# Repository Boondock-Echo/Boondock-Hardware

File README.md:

# Boondock-Hardware
Hardware Design Files, BOM, Assembly Instructions, etc.

# Hardware

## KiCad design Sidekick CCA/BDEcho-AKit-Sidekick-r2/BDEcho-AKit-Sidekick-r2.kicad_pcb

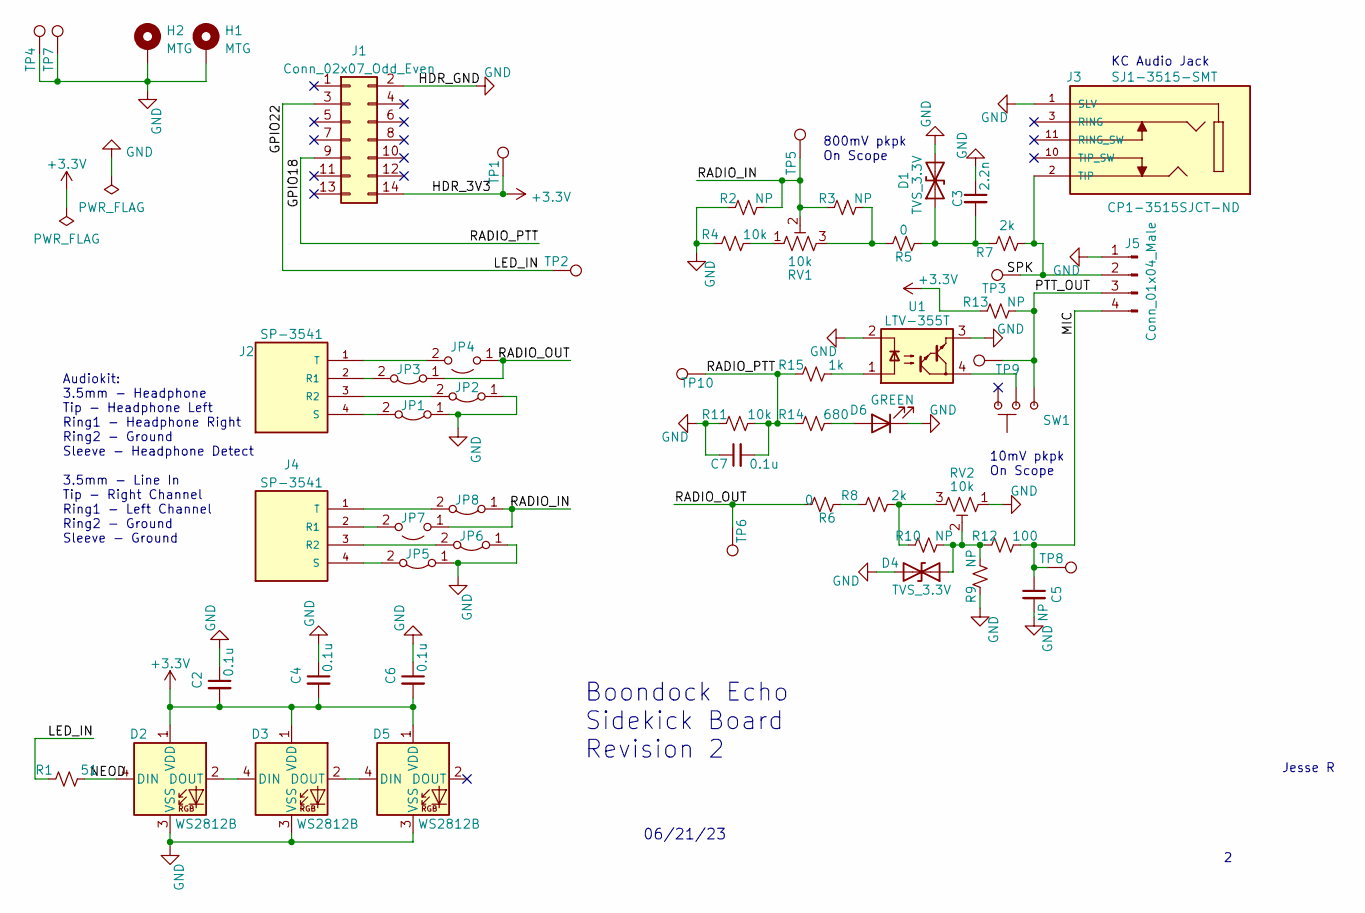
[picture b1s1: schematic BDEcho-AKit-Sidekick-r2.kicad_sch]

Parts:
C2, C4, C6, C7: 0.1u; C_0805_2012Metric; LCSC C1711
C3: 2.2n; C_0805_2012Metric; MFG # CL21C222JBFNNNE; JLCPCB C28260
C5: NP; C_0805_2012Metric; MFG # NA; JLCPCB NA
D1, D4: TVS_3.3V; D_SOD-123; MFG # BZT52C3V3; JLCPCB C2891770
D2, D3, D5: WS2812B; LED_WS2812B_PLCC4; MFG # WS2812B-B/W; JLCPCB C2761795
D6: GREEN; LED_0805_2012Metric; LCSC C73548
H1, H2: MTG; MountingHole_2.7mm_M2.5_ISO7380_Pad; LCSC NA
J1: Conn_02x07_Odd_Even; PinHeader_2x07_P2.54mm_Vertical; LCSC C400039
J2, J4: SP-3541; SP-3541_Makerfabs_2; PART_REV 1.0; LCSC MFABS
J3: SJ1-3515-SMT; CUI_SJ1-3515-SMT; PARTREV 1.05; JLCPCB NA
J5: Conn_01x04_Male; PinHeader_1x04_P2.54mm_Vertical; LCSC NA
JP1, JP2, JP3, JP5, JP6, JP8: JMP; SolderJumper-2_P1.3mm_Bridged2Bar_RoundedPad1.0x1.5mm; LCSC NA
JP4, JP7: JMP; SolderJumper-2_P1.3mm_Open_RoundedPad1.0x1.5mm; LCSC NA
R1: 51; R_0805_2012Metric; LCSC C17738
R2, R3, R9, R10: NP; R_0805_2012Metric; MFG # 0805W8F0000T5E; JLCPCB C17477
R4, R11: 10k; R_0805_2012Metric; LCSC C17414
R5, R6: 0; R_0805_2012Metric; MFG # 0805W8F0000T5E; JLCPCB C17477
R7, R8: 2k; R_0805_2012Metric; LCSC C17604
R12: 100; R_0805_2012Metric; LCSC C17408
R13: NP; R_0805_2012Metric
R14: 680; R_0805_2012Metric; MFG # 0805W8F6800T5E; JLCPCB C17798
R15: 1k; R_0805_2012Metric; LCSC C17513
RV1, RV2: 10k; TRIM_3314J-1-103E; LCSC C36376
SW1: SW_SLIDE_SPDT; SW_JS102011SAQN; LCSC C221660
TP1, TP2, TP3, TP4, TP5, TP6, TP7, TP8, TP9, TP10: TP; TestPoint_THTPad_1.0x1.0mm_Drill0.5mm; MFG # NA; JLCPCB NA
U1: LTV-355T; SO-4_4.4x3.6mm_P2.54mm; MFG # LTV-355T; JLCPCB C10803

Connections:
+3.3V: C2.2, C4.2, C6.2, D2.1 (VDD), D3.1 (VDD), D5.1 (VDD), J1.14, R13.1, TP1.1
/GPIO18: C7.2, J1.9, R11.1, R14.2, R15.2, TP10.1
/GPIO22: J1.3, R1.2, TP2.1
/MIC: C5.1, J5.4, R12.1, TP8.1
/NEOD: D2.4 (DIN), R1.1
/PTT_OUT: J5.3, R13.2, SW1.3 (NO), TP9.1
/RADIO_IN: JP7.1 (A), JP8.1 (A), R2.2, R3.1, RV1.2, TP5.1
/RADIO_OUT: JP3.1 (A), JP4.1 (A), R6.1, TP6.1
/SPK: J3.2 (TIP), J5.2, R7.1, TP3.1
GND: C2.1, C3.1, C4.1, C5.2, C6.1, C7.1, D1.2 (A2), D2.3 (VSS), D3.3 (VSS), D4.2 (A2), D5.3 (VSS), D6.1 (K), H1.1, H2.1, J1.2, J3.1 (SLV), J5.1, JP1.1 (A), JP2.1 (A), JP5.1 (A), JP6.1 (A), R2.1, R4.2, R9.1, R11.2, RV2.1, TP4.1, TP7.1, U1.2, U1.3
unnamed: C3.2, D1.1 (A1), R5.2, R7.2
unnamed: D2.2 (DOUT), D3.4 (DIN)
unnamed: D3.2 (DOUT), D5.4 (DIN)
unnamed: D4.1 (A1), R9.2, R10.2, R12.2, RV2.2
unnamed: D6.2 (A), R14.1
unnamed: J2.1 (T), JP4.2 (B)
unnamed: J2.2 (R1), JP3.2 (B)
unnamed: J2.3 (R2), JP2.2 (B)
unnamed: J2.4 (S), JP1.2 (B)
unnamed: J4.1 (T), JP8.2 (B)
unnamed: J4.2 (R1), JP7.2 (B)
unnamed: J4.3 (R2), JP6.2 (B)
unnamed: J4.4 (S), JP5.2 (B)
unnamed: R3.2, R5.1, RV1.3
unnamed: R4.1, RV1.1
unnamed: R6.2, R8.2
unnamed: R8.1, R10.1, RV2.3
unnamed: R15.1, U1.1
unnamed: SW1.2 (CO), U1.4

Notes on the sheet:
10mV pkpk On Scope
800mV pkpk On Scope
KC Audio Jack
Audiokit: 3.5mm - Headphone Tip - Headphone Left Ring1 - Headphone Right Ring2 - Ground Sleeve - Headphone Detect 3.5mm - Line In Tip - Right Channel Ring1 - Left Channel Ring2 - Ground Sleeve - Ground
Boondock Echo Sidekick Board Revision 2
Jesse R
06/21/23

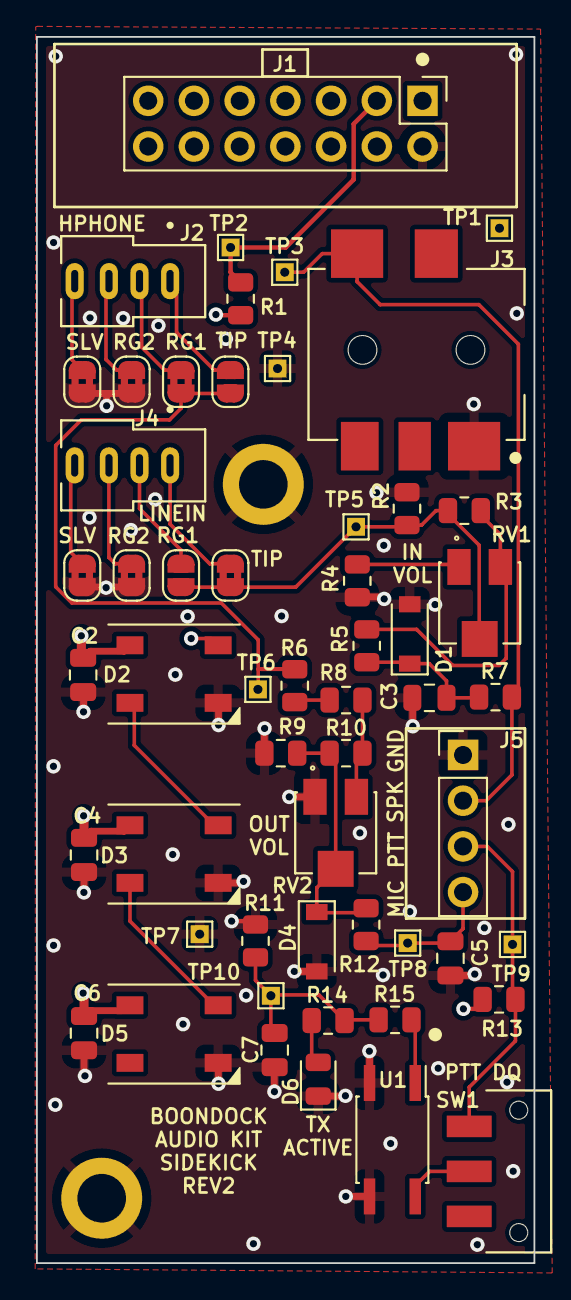
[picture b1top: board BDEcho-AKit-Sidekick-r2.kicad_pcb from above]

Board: 4 copper layers, 27.6 x 68.1 mm, 56 parts (0 on the bottom side), 29 nets.

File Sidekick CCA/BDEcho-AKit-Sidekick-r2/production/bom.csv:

Designator,Footprint,Quantity,Value,LCSC Part #
"C2, C4, C6, C7",C_0805_2012Metric,4,0.1u,C1711
C3,C_0805_2012Metric,1,2.2n,C28260
"D1, D4",D_SOD-123,2,TVS_3.3V,C2891770
"D2, D3, D5",LED_WS2812B_PLCC4,3,WS2812B,C2761795
D6,LED_0805_2012Metric,1,GREEN,C73548
J1,PinHeader_2x07_P2.54mm_Vertical,1,Conn_02x07_Odd_Even,C400039
"J2, J4",SP-3541_Makerfabs_2,2,SP-3541,MFABS
R1,R_0805_2012Metric,1,51,C17738
"R11, R4",R_0805_2012Metric,2,10k,C17414
R12,R_0805_2012Metric,1,100,C17408
R14,R_0805_2012Metric,1,680,C17798
R15,R_0805_2012Metric,1,1k,C17513
"R5, R6",R_0805_2012Metric,2,0,C17477
"R7, R8",R_0805_2012Metric,2,2k,C17604
"RV1, RV2",TRIM_3314J-1-103E,2,10k,C36376
SW1,SW_JS102011SAQN,1,SW_SLIDE_SPDT,C221660
U1,SO-4_4.4x3.6mm_P2.54mm,1,LTV-355T,C10803

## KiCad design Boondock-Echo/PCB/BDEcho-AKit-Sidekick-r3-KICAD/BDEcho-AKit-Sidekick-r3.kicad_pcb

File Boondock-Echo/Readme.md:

# Boondock-Echo 
Hardware Design Files, BOM, Assembly Instructions, etc.

# 3D Files
Complete set of 3D .stl files for printing

# Case
This is the shipping box

# ESP32 Audiokit

# PCB
The KiCad design files for the board

# Software
The firmware for this project is in a different repository.  The easiest way to get started is to create an account at boondockecho.com and do a "firmware upgrade" process there.  Accounts are free.

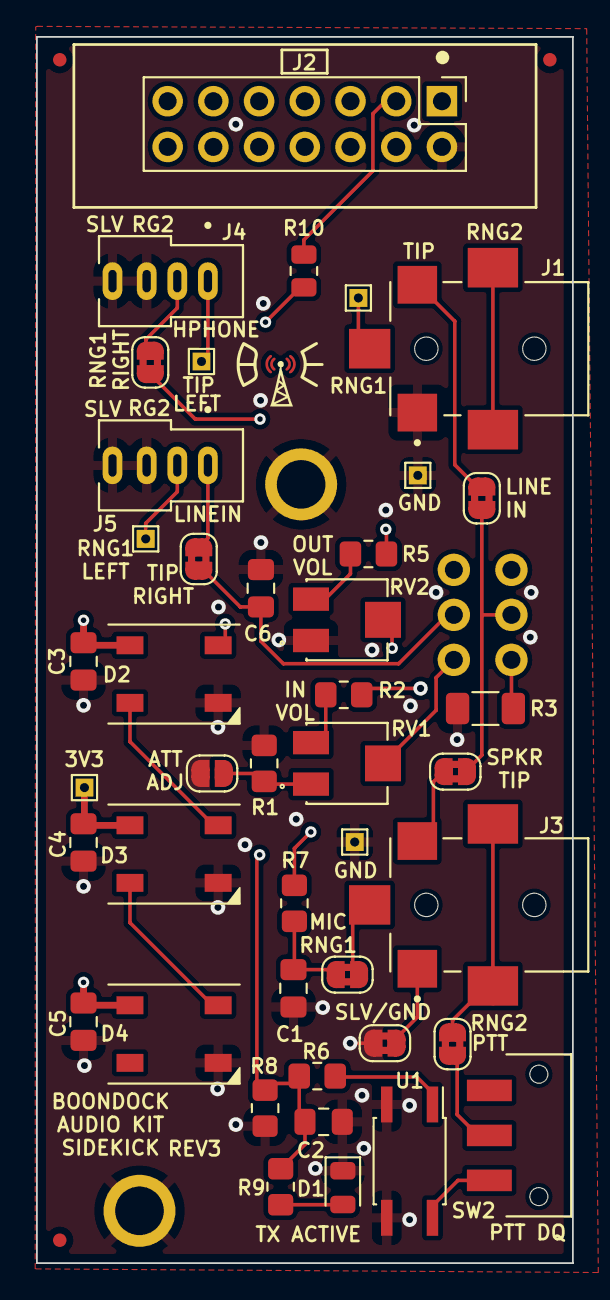
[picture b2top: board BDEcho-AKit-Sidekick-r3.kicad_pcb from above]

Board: 4 copper layers, 29.8 x 68.1 mm, 49 parts (1 on the bottom side), 32 nets.

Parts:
C1, C6: NP; C_0805_2012Metric_Pad1.18x1.45mm_HandSolder
C2, C3, C4, C5: 0.1u; C_0805_2012Metric_Pad1.18x1.45mm_HandSolder
D1: GREEN; LED_0805_2012Metric
D2, D3, D4: WS2812B; LED_WS2812B_PLCC4
FID1, FID2, FID3: Fiducial; Fiducial_0.75mm_Mask1.5mm
H1, H2: MTG; MountingHole_2.7mm_M2.5_ISO7380_Pad
J1, J3: SJ2-3594A-SMT-TR
J2: Conn_02x07_Odd_Even; PinHeader_2x07_P2.54mm_Vertical
J4, J5: SP-3541; SP-3541_PCBWay
JP1, JP2, JP3, JP4, JP5, JP7, JP8: JMP; SolderJumper-2_P1.3mm_Bridged2Bar_RoundedPad1.0x1.5mm
JP6: Jumper_2_Open; SolderJumper-2_P1.3mm_Open_RoundedPad1.0x1.5mm
LOGO1: Fiducial; LOGO
R1: 3.3k; R_0805_2012Metric_Pad1.20x1.40mm_HandSolder
R2: 5.1k; R_0805_2012Metric_Pad1.20x1.40mm_HandSolder
R3: NP; R_1206_3216Metric_Pad1.30x1.75mm_HandSolder
R5, R6: 1k; R_0805_2012Metric_Pad1.20x1.40mm_HandSolder
R7: 100; R_0805_2012Metric_Pad1.20x1.40mm_HandSolder
R8: 10k; R_0805_2012Metric_Pad1.20x1.40mm_HandSolder
R9: 680; R_0805_2012Metric_Pad1.20x1.40mm_HandSolder
R10: 51; R_0805_2012Metric
RV1, RV2: 5k; TRIM_3314J-1-103E
SW1: JS202011CQN
SW2: SW_SLIDE_SPDT; SW_JS102011SAQN
TP1, TP2, TP3, TP4, TP6, TP9: TP; TestPoint_THTPad_1.0x1.0mm_Drill0.5mm
U1: LTV-355T; SO-4_4.4x3.6mm_P2.54mm

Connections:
+3.3V: C3.2, C4.2, C5.2, D2.1 (VDD), D3.1 (VDD), D4.1 (VDD), J2.14, TP4.1
/AFIN: C1.1, JP4.2 (B), R7.1
/AFOUT: J3.2, JP5.1 (A)
/ATT_IN: R2.1, R3.2, SW1.1
/ATT_OUT: RV1.2, SW1.4
/COMBAUD: JP1.2 (B), JP5.2 (B), SW1.2
/GPIO18: C2.2, J2.9, R6.2, R8.1, R9.2
/GPIO22: J2.3, R10.2
/LINEIN: J1.2, JP1.1 (A)
/NEOD: D2.4 (DIN), R10.1
/PTT: JP3.2 (B), SW2.2 (CO)
/RADIO_IN: C6.1, JP8.1 (A), SW1.5
/RADIO_OUT: JP7.1 (A), R5.2
GND: C1.2, C2.1, C3.1, C4.1, C5.1, C6.2, D1.1 (K), D2.3 (VSS), D3.3 (VSS), D4.3 (VSS), H1.1, H2.1, J1.1, J2.2, J4.3 (R2), J4.4 (S), J5.3 (R2), J5.4 (S), JP2.2 (B), JP6.2 (B), R1.2, R3.1, R8.2, RV2.1, TP1.1, TP2.1, U1.2, U1.3
unnamed: D1.2 (A), R9.1
unnamed: D2.2 (DOUT), D3.4 (DIN)
unnamed: D3.2 (DOUT), D4.4 (DIN)
unnamed: J1.3, TP3.1
unnamed: J3.1, JP2.1 (A)
unnamed: J3.3, JP4.1 (A)
unnamed: J3.4_1, J3.4_2, JP3.1 (A)
unnamed: J4.1 (T), TP6.1
unnamed: J4.2 (R1), JP7.2 (B)
unnamed: J5.1 (T), JP8.2 (B)
unnamed: J5.2 (R1), TP9.1
unnamed: JP6.1 (A), R1.1, RV1.1
unnamed: R2.2, RV1.3
unnamed: R5.1, RV2.3
unnamed: R6.1, U1.1
unnamed: R7.2, RV2.2
unnamed: SW1.3, SW1.6
unnamed: SW2.1 (NC), U1.4

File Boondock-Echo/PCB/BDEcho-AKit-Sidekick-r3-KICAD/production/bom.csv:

Designator,Footprint,Quantity,Value,LCSC Part #
"C1, C6",C_0805_2012Metric_Pad1.18x1.45mm_HandSolder,2,NP,NA
"C2, C3, C4, C5",C_0805_2012Metric_Pad1.18x1.45mm_HandSolder,4,0.1u,C49678
D1,LED_0805_2012Metric,1,GREEN,C73548
"D2, D3, D4",LED_WS2812B_PLCC4,3,WS2812B,C2761795
"FID1, FID2, FID3",Fiducial_0.75mm_Mask1.5mm,3,Fiducial,NA
"H1, H2",MountingHole_2.7mm_M2.5_ISO7380_Pad,2,MTG,NA
"J1, J3",SJ2-3594A-SMT-TR,2,SJ2-3594A-SMT-TR,
J2,PinHeader_2x07_P2.54mm_Vertical,1,Conn_02x07_Odd_Even,C400039
"J4, J5",SP-3541_PCBWay,2,SP-3541,MFABS
"JP1, JP2, JP3, JP4, JP5, JP7, JP8",SolderJumper-2_P1.3mm_Bridged2Bar_RoundedPad1.0x1.5mm,7,JMP,NA
JP6,SolderJumper-2_P1.3mm_Open_RoundedPad1.0x1.5mm,1,Jumper_2_Open,NA
LOGO,LOGO,1,Fiducial,
R1,R_0805_2012Metric_Pad1.20x1.40mm_HandSolder,1,3.3k,C26010
R10,R_0805_2012Metric,1,51,C17738
R2,R_0805_2012Metric_Pad1.20x1.40mm_HandSolder,1,5.1k,C27834
R3,R_1206_3216Metric_Pad1.30x1.75mm_HandSolder,1,NP,NA
"R5, R6",R_0805_2012Metric_Pad1.20x1.40mm_HandSolder,2,1k,C17513
R7,R_0805_2012Metric_Pad1.20x1.40mm_HandSolder,1,100,C17408
R8,R_0805_2012Metric_Pad1.20x1.40mm_HandSolder,1,10k,C17414
R9,R_0805_2012Metric_Pad1.20x1.40mm_HandSolder,1,680,C17798
"RV1, RV2",TRIM_3314J-1-103E,2,5k,C58391
SW1,JS202011CQN,1,JS202011CQN,C221663
SW2,SW_JS102011SAQN,1,SW_SLIDE_SPDT,C221660
"TP1, TP2, TP3, TP4, TP6, TP9",TestPoint_THTPad_1.0x1.0mm_Drill0.5mm,6,TP,NA
U1,SO-4_4.4x3.6mm_P2.54mm,1,LTV-355T,C10803

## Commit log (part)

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2023-10-02 First commit of hardware files
    First commit of hardware files, contains kicad CCA files, manufacturing files, 3D files, schematic for purchased audio kit board, some assembly notes, assembly bom
2023-10-10 Add files via upload
    Updated back for a little more room around board
2023-10-17 Add files via upload
    Updated back, front, and buttons
2023-10-27 Add files via upload
    Updated STLs and tinkercad link
2023-10-27 Delete 3D Files directory
    Need to refresh Files
2023-10-27 Add files via upload
    Added 3D Files and up to date TinkerCAD link
2024-09-01 Delete 3D Files directory
    Removing very old files and updating
2024-09-01 Create Readme.txt
    Initial Commit
2024-09-01 Create 3D Files
2024-09-01 Add files via upload
    RC02 files
2024-09-11 Add separate files for buttons and slide switch
2025-03-05 Delete ElectricalAssembly-BOM.csv
    Removing all old design files and uploading a fresh batch
2025-03-05 Delete Assembly Notes directory
    Removing all old files for refresh
2025-03-05 Delete ESP32-Audiokit directory
    Removing all of the old design files for a refresh
2025-03-05 Delete Hardware directory
    Removing all the old design files for a refresh
2025-03-05 Add files via upload
    3D print files for the Boondock Echo RC03
2025-03-05 Add files via upload
    Assembly Instrucitons and Files
2025-03-05 Add files via upload
    The shipping box design files.
2025-03-05 Delete Case directory
    Wrong location
2025-03-05 Add files via upload
    Adding All the PCB Files
2025-03-10 Create Readme.md
    Initial Commit
2025-03-10 Add files via upload
    Initial Commit
2025-03-10 Update Readme.md
    Added 3d Model in Readme.
2025-03-10 Organized files and added information to the readme.md
    Organized files and added information to the readme.md
2025-03-10 File reoganization
2025-03-10 Added .stl and image
2025-03-11 Adding Video and Changing Folder Structure
2025-03-11 Add Assembly Gif
2025-03-11 Update Readme.md
    Added an assembly .gif
2025-03-14 Rename USB_DovetailSlide (1).stl to USB_DovetailSlide.stl
2025-07-10 Fixing the multiple products with duplicate names issue
    We have several products sharing the "Tango" name -- moving the large scanner carrier to Boondock Hotel, the small box to Boondock Tango, and the scanner controller to Boondock Wilco. While the large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
2025-07-10 Update Readme.md
    Fixing Links
2025-07-10 Update Readme.md
    Fixing Broken Links from Renaming everything.
2025-07-15 Adding Assembly Gif back in.
    Adding Assembly Gif back in.
2026-02-16 Tango STL files
